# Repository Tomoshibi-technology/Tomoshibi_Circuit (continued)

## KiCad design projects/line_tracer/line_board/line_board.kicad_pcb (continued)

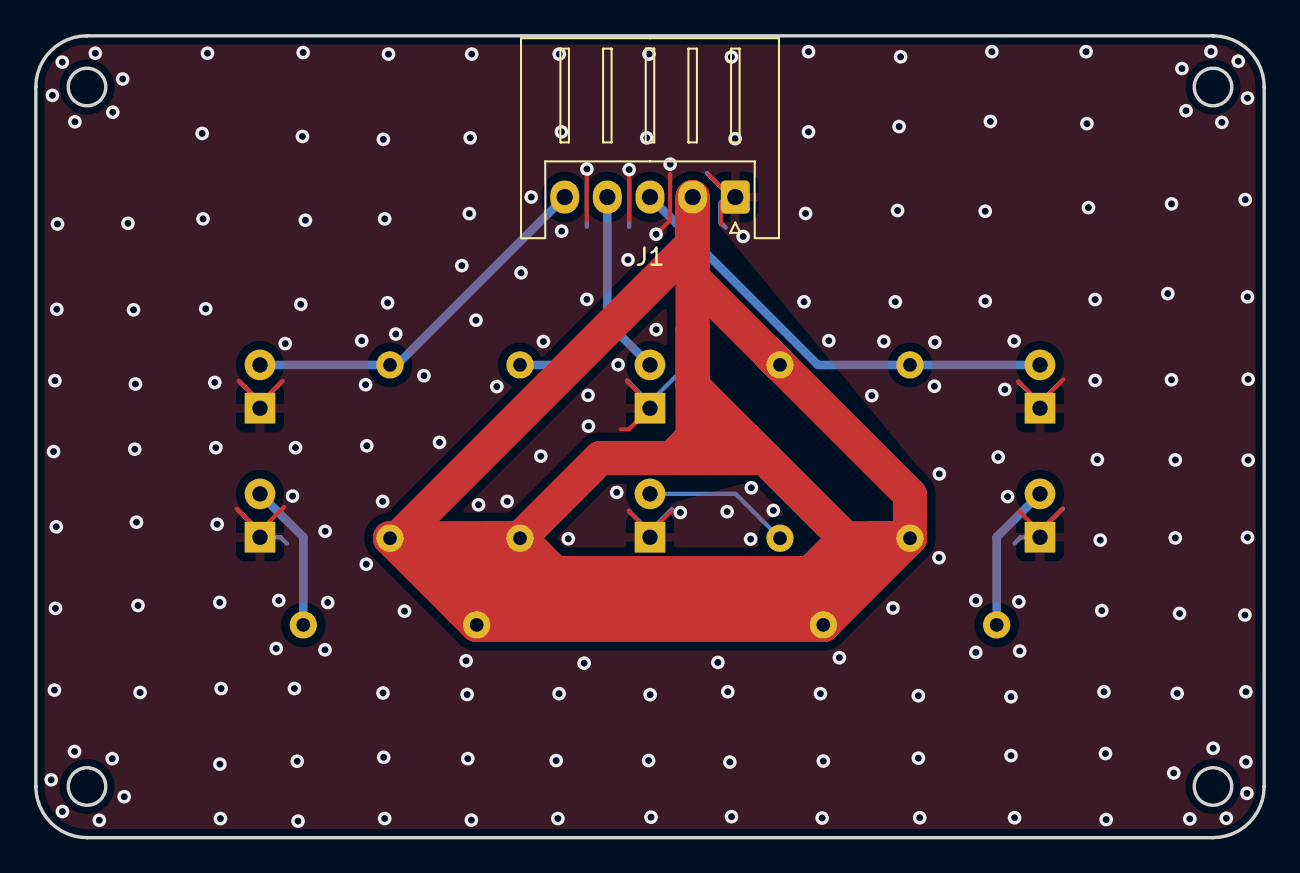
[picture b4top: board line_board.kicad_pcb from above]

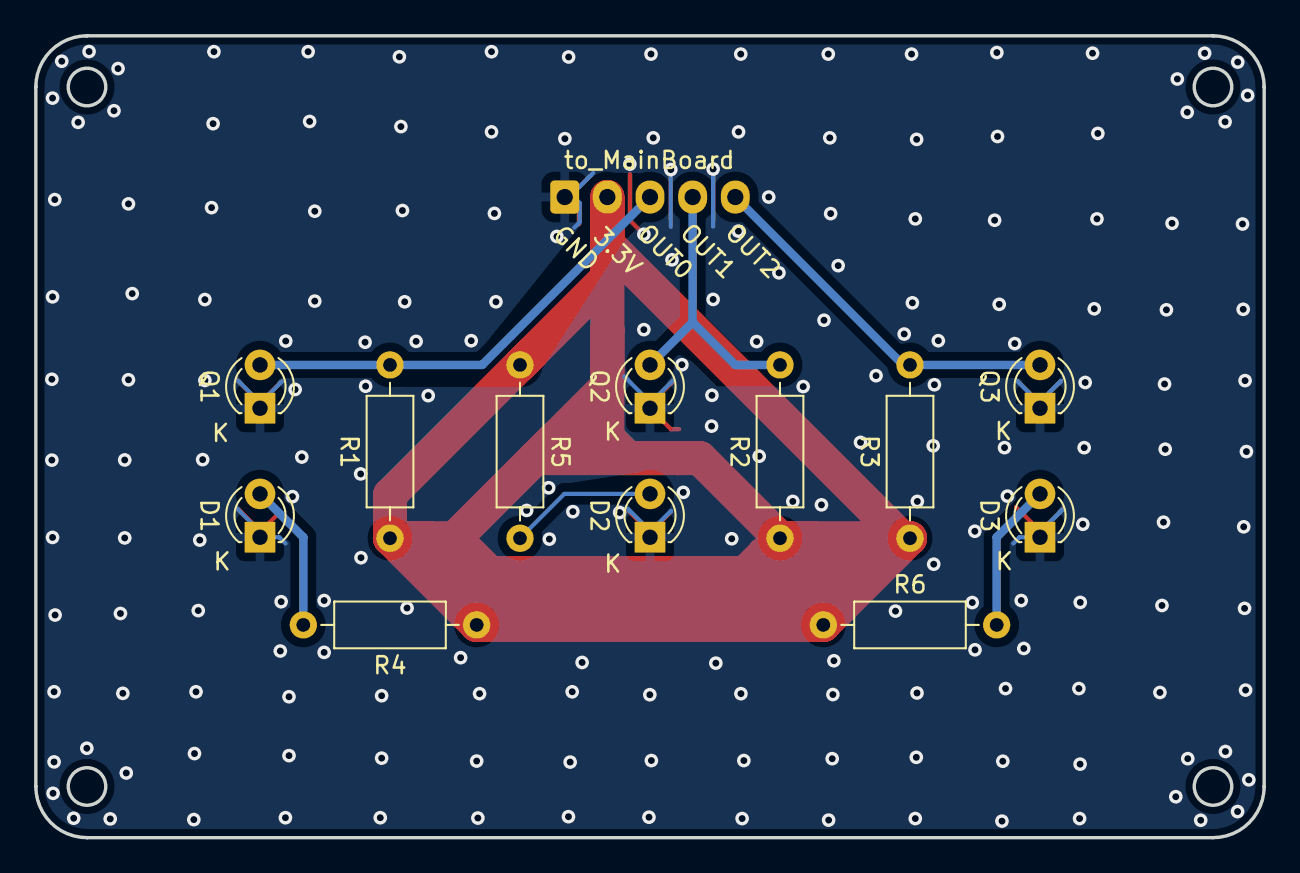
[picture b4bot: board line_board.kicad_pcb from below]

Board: 2 copper layers, 72.0 x 47.0 mm, 13 parts (12 on the bottom side), 8 nets.

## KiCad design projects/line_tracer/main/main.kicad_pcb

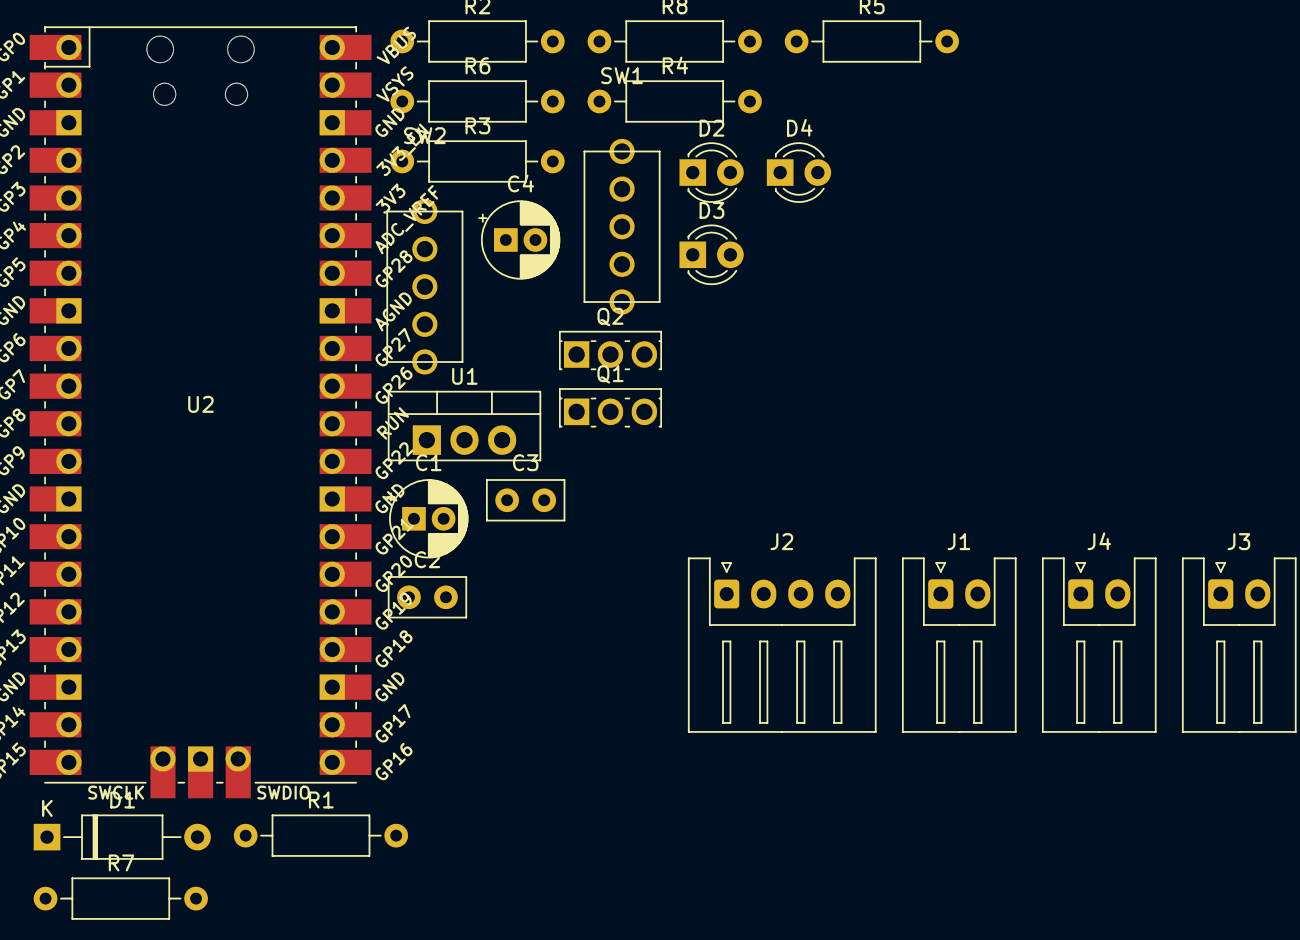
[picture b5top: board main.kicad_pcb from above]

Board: 2 copper layers, 26 parts (0 on the bottom side), 19 nets, no tracks yet.

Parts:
C1, C4: 100u; CP_Radial_D5.0mm_P2.00mm
C2, C3: 0.1u; C_Disc_D5.0mm_W2.5mm_P2.50mm
D1: D; D_A-405_P10.16mm_Horizontal
D2, D3, D4: LED; LED_D3.0mm
J1, J3, J4: Conn_01x02_Female; JST_XH_S2B-XH-A_1x02_P2.50mm_Horizontal
J2: Conn_01x04_Female; JST_XH_S4B-XH-A_1x04_P2.50mm_Horizontal
Q1, Q2: Q_PMOS_GDS; SIPAK_Vertical
R1, R4, R6, R7, R8: 1k; R_Axial_DIN0207_L6.3mm_D2.5mm_P10.16mm_Horizontal
R2, R3, R5: 10k; R_Axial_DIN0207_L6.3mm_D2.5mm_P10.16mm_Horizontal
SW1, SW2: SW_SPDT; 3P_SPDT_5Pin_ToggleSwitch
U1: LM7805_TO220; TO-220-3_Vertical
U2: Pico; RPi_Pico_SMD_TH

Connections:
+3.3V: J2.2, SW1.2 (B), SW2.2 (B), U2.36 (3V3)
+5V: C3.1, C4.1, Q2.3 (S), R5.1, U1.3 (VO)
+6V: J1.2, Q1.2 (D)
GND: C1.2, C2.2, C3.2, C4.2, J1.1, J2.1, R1.1, R2.1, R3.1, R6.1, R7.1, R8.1, SW1.1 (A), SW2.1 (A), U1.2 (GND), U2.3 (GND), U2.8 (GND), U2.13 (GND), U2.18 (GND), U2.23 (GND), U2.28 (GND), U2.33 (AGND), U2.38 (GND)
LED0: D3.2 (A), U2.29 (GPIO22)
LED1: D4.2 (A), U2.34 (GPIO28_ADC2)
unnamed: D1.1 (K), U2.39 (VSYS)
unnamed: D1.2 (A), D2.2 (A), Q2.2 (D)
unnamed: D2.1 (K), R6.2
unnamed: D3.1 (K), R7.2
unnamed: D4.1 (K), R8.2
unnamed: Q1.1 (G), R1.2
unnamed: Q2.1 (G), R4.2, R5.2
unnamed: R4.1, U2.40 (VBUS)
VM: C1.1, C2.1, Q1.3 (S), U1.1 (VI)
sesor_input0: J2.3, U2.31 (GPIO26_ADC0)
sesor_input1: J2.4, U2.32 (GPIO27_ADC1)
switch0: R2.2, U2.26 (GPIO20)
switch1: R3.2, U2.27 (GPIO21)
